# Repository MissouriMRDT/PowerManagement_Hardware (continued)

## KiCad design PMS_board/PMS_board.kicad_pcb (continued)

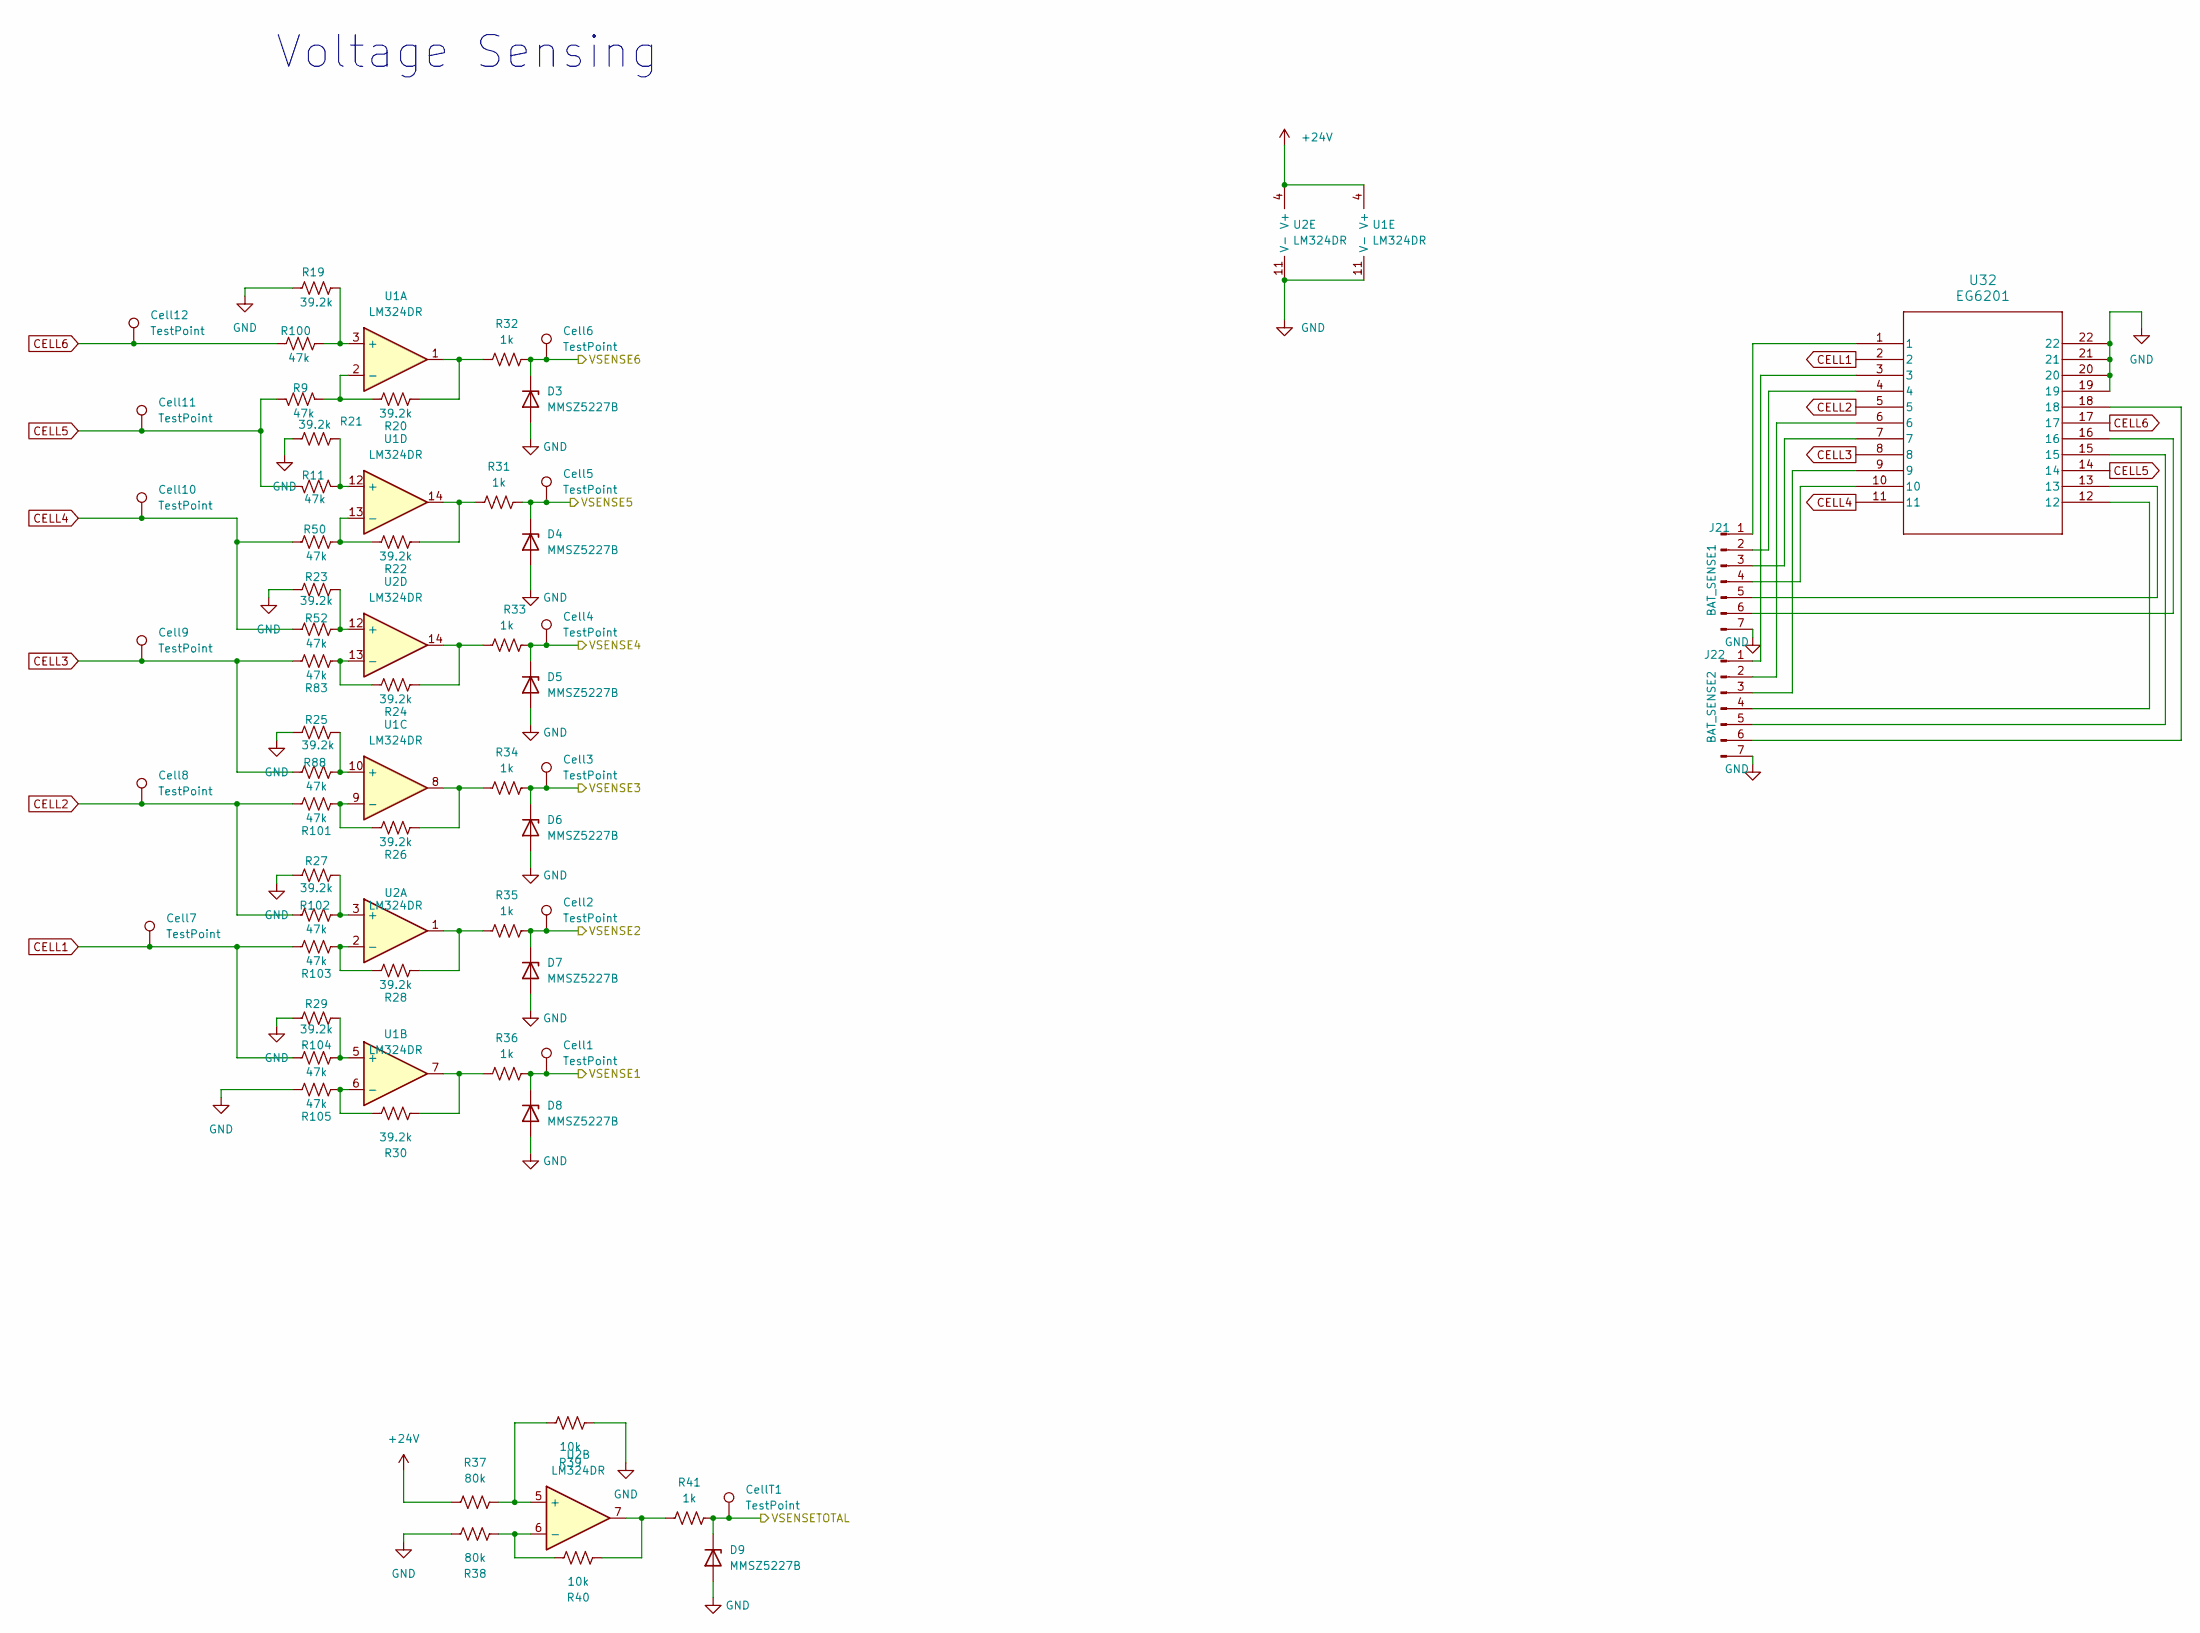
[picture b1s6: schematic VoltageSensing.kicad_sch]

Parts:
Cell1, Cell2, Cell3, Cell4, Cell5, Cell6, Cell7, Cell8, Cell9, Cell10, Cell11, Cell12: TestPoint; TestPoint_Pad_D1.0mm
CellT1: TestPoint; TestPoint_Pad_D1.0mm
D3, D4, D5, D6, D7, D8, D9: MMSZ5227B; D_SOD-123
J21: BAT_SENSE1; MOLEX_SL_07_Vertical
J22: BAT_SENSE2; MOLEX_SL_07_Vertical
R9, R11, R50, R52, R83, R88, R100, R101, R102, R103, R104, R105: 47k; R_0603_1608Metric_Pad0.98x0.95mm_HandSolder
R19, R20, R21, R22, R23, R24, R25, R26, R27, R28, R29, R30: 39.2k; R_0603_1608Metric_Pad0.98x0.95mm_HandSolder
R31, R32, R33, R34, R35, R36, R41: 1k; R_0603_1608Metric_Pad0.98x0.95mm_HandSolder
R37, R38: 80k; R_0603_1608Metric_Pad0.98x0.95mm_HandSolder
R39, R40: 10k; R_0603_1608Metric_Pad0.98x0.95mm_HandSolder
U1, U2: LM324DR; SOIC-14_3.9x8.7mm_P1.27mm
U32: EG6201; DIP_G6201_EWI

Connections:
+24V: R37.1, U1.4 (V+), U2.4 (V+); also elsewhere on the board
/Microcontroller/VSENSE1: Cell1.1 (1_1), D8.1 (K), R36.2; also elsewhere on the board
/Microcontroller/VSENSE3: Cell3.1 (1_1), D6.1 (K), R34.2; also elsewhere on the board
/Microcontroller/VSENSE4: Cell4.1 (1_1), D5.1 (K), R33.2; also elsewhere on the board
/Microcontroller/VSENSE6: Cell6.1 (1_1), D3.1 (K), R32.2; also elsewhere on the board
/Microcontroller/VSenseT: CellT1.1 (1_1), D9.1 (K), R41.2; also elsewhere on the board
CELL1: Cell7.1, R103.1, R104.1, U32.2; also elsewhere on the board
CELL3: Cell9.1, R83.1, R88.1, U32.8; also elsewhere on the board
CELL4: Cell10.1, R50.1, R52.1, U32.11; also elsewhere on the board
CELL6: Cell12.1, R100.1, U32.17; also elsewhere on the board
GND: D3.2 (A), D4.2 (A), D5.2 (A), D6.2 (A), D7.2 (A), D8.2 (A), D9.2 (A), J21.7, J22.7, R19.2, R21.2, R23.2, R25.2, R27.2, R29.2, R38.2, R39.2, R105.1, U1.11 (V-), U2.11 (V-), U32.19, U32.20, U32.21, U32.22; also elsewhere on the board
unnamed: J21.1, U32.1
unnamed: J21.2, U32.4
unnamed: J21.3, U32.7
unnamed: J21.4, U32.10
unnamed: J21.5, U32.13
unnamed: J21.6, U32.16
unnamed: J22.1, U32.3
unnamed: J22.2, U32.6
unnamed: J22.3, U32.9
unnamed: J22.4, U32.12
unnamed: J22.5, U32.15
unnamed: J22.6, U32.18
unnamed: R20.2, R32.1, U1.1
unnamed: R22.2, R31.1, U1.14
unnamed: R24.2, R33.1, U2.14
unnamed: R26.2, R34.1, U1.8
unnamed: R28.2, R35.1, U2.1
unnamed: R30.2, R36.1, U1.7
unnamed: R40.2, R41.1, U2.7
unnamed: R19.1, R100.2, U1.3 (+)
unnamed: R9.1, R20.1, U1.2 (-)
unnamed: R29.1, R104.2, U1.5 (+)
unnamed: R30.1, R105.2, U1.6 (-)
unnamed: R25.1, R88.2, U1.10 (+)
unnamed: R26.1, R101.2, U1.9 (-)
unnamed: R11.1, R21.1, U1.12 (+)
unnamed: R22.1, R50.2, U1.13 (-)
unnamed: R27.1, R102.2, U2.3 (+)
unnamed: R28.1, R103.2, U2.2 (-)
unnamed: R37.2, R39.1, U2.5 (+)
unnamed: R38.1, R40.1, U2.6 (-)
unnamed: R23.1, R52.2, U2.12 (+)
unnamed: R24.1, R83.2, U2.13 (-)

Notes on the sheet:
Voltage Sensing

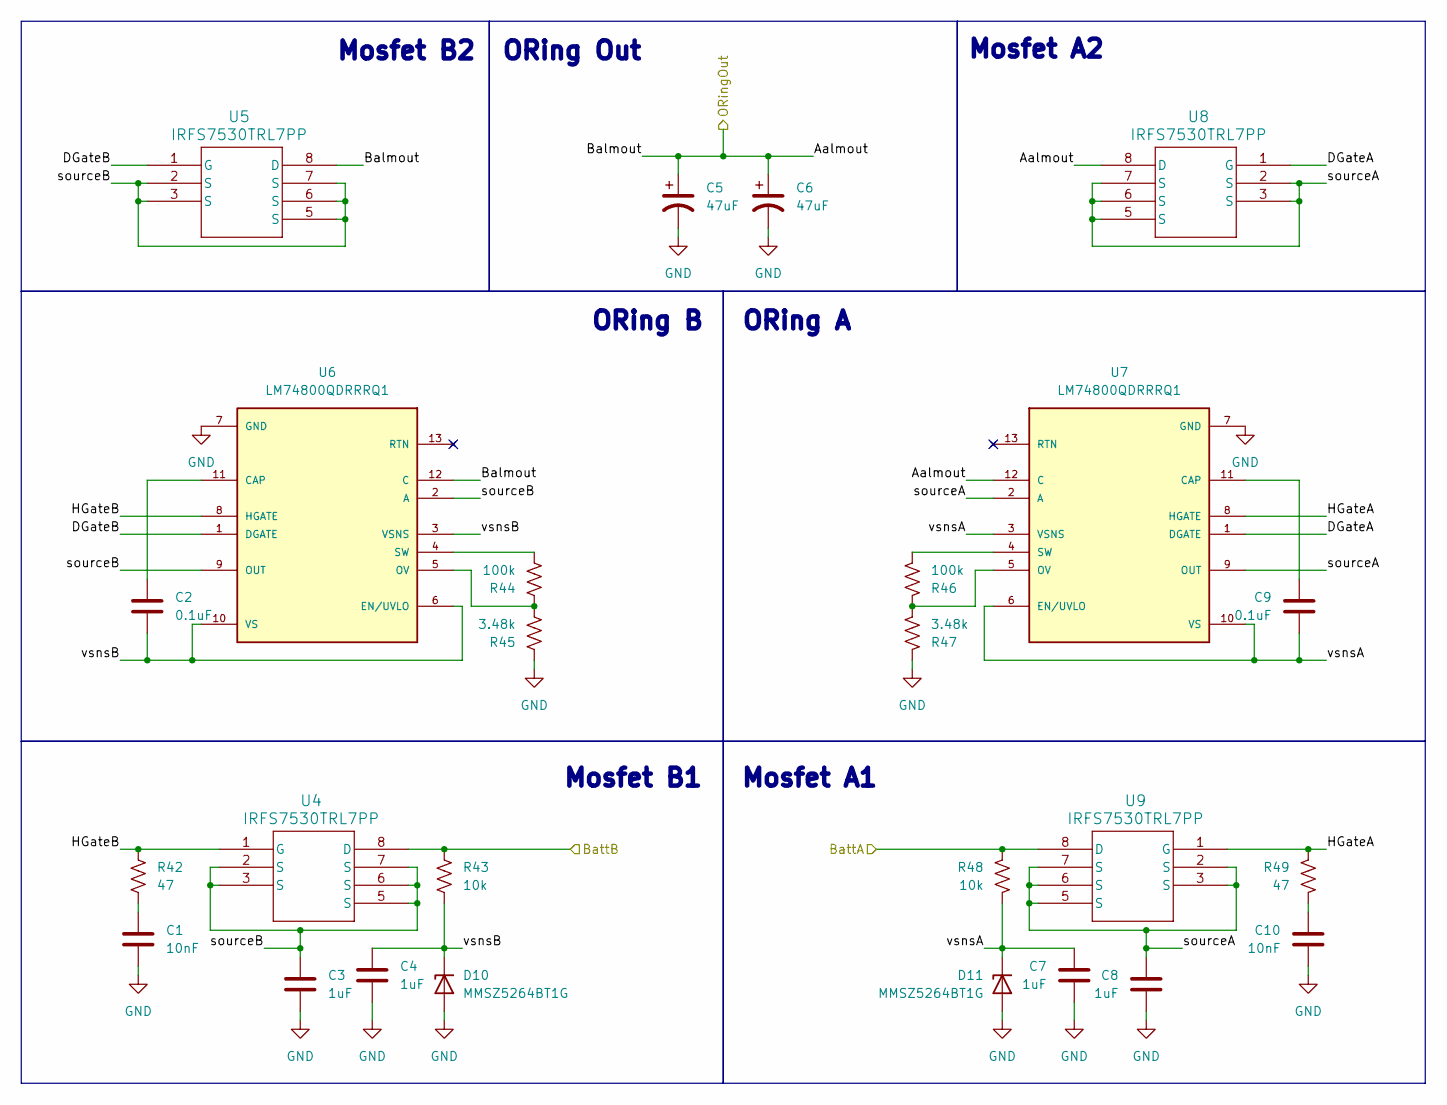
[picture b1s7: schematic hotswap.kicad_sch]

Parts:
C1, C10: 10nF; C_0603_1608Metric_Pad1.08x0.95mm_HandSolder
C2, C9: 0.1uF; C_0603_1608Metric_Pad1.08x0.95mm_HandSolder
C3, C4, C7, C8: 1uF; C_0603_1608Metric_Pad1.08x0.95mm_HandSolder
C5, C6: 47uF; C_0603_1608Metric_Pad1.08x0.95mm_HandSolder
D10, D11: MMSZ5264BT1G; D_SOD-123
R42, R49: 47; R_0603_1608Metric_Pad0.98x0.95mm_HandSolder
R43, R48: 10k; R_0603_1608Metric_Pad0.98x0.95mm_HandSolder
R44, R46: 100k; R_0603_1608Metric_Pad0.98x0.95mm_HandSolder
R45, R47: 3.48k; R_0603_1608Metric_Pad0.98x0.95mm_HandSolder
U4, U5, U8, U9: IRFS7530TRL7PP; PG-TO263-7_INF
U6, U7: LM74800QDRRRQ1; IC_LM74800QDRRRQ1; PARTREV C

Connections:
/HotSwap/Aalmout: C5.1, C6.1, U5.8 (D), U6.12 (C), U7.12 (C), U8.8 (D); also elsewhere on the board
/HotSwap/DGateA: U7.1 (DGATE), U8.1 (G)
/HotSwap/DGateB: U5.1 (G), U6.1 (DGATE)
/HotSwap/HGateA: R49.1, U7.8 (HGATE), U9.1 (G)
/HotSwap/HGateB: R42.1, U4.1 (G), U6.8 (HGATE)
/HotSwap/sourceA: C8.1, U7.2 (A), U7.9 (OUT), U8.2 (S), U8.3 (S), U8.5 (S), U8.6 (S), U8.7 (S), U9.2 (S), U9.3 (S), U9.5 (S), U9.6 (S), U9.7 (S)
/HotSwap/sourceB: C3.1, U4.2 (S), U4.3 (S), U4.5 (S), U4.6 (S), U4.7 (S), U5.2 (S), U5.3 (S), U5.5 (S), U5.6 (S), U5.7 (S), U6.2 (A), U6.9 (OUT)
/HotSwap/vsnsA: C7.1, C9.2, D11.1 (K), R48.1, U7.3 (VSNS), U7.6 (EN/UVLO), U7.10 (VS)
/HotSwap/vsnsB: C2.2, C4.1, D10.1 (K), R43.1, U6.3 (VSNS), U6.6 (EN/UVLO), U6.10 (VS)
BATTERY_IN1: R48.2, U9.8 (D); also elsewhere on the board
BATTERY_IN2: R43.2, U4.8 (D); also elsewhere on the board
GND: C1.2, C3.2, C4.2, C5.2, C6.2, C7.2, C8.2, C10.2, D10.2 (A), D11.2 (A), R45.1, R47.1, U6.7 (GND), U7.7 (GND); also elsewhere on the board
unnamed: C1.1, R42.2
unnamed: C10.1, R49.2
unnamed: C2.1, U6.11 (CAP)
unnamed: R44.1, R45.2, U6.5 (OV)
unnamed: R44.2, U6.4 (SW)
unnamed: C9.1, U7.11 (CAP)
unnamed: R46.1, R47.2, U7.5 (OV)
unnamed: R46.2, U7.4 (SW)

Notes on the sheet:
ORing B
ORing Out
Mosfet A1
Mosfet B1
ORing A
Mosfet A2
Mosfet B2

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
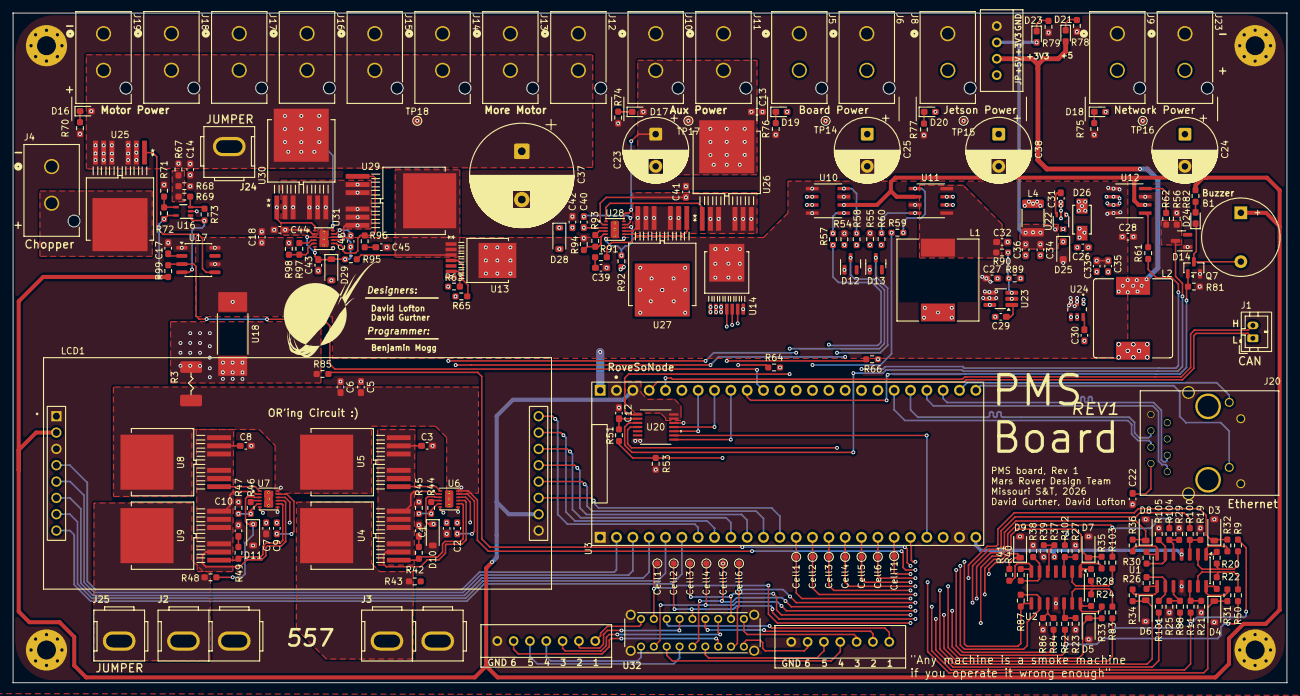
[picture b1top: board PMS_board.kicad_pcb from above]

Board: 4 copper layers, 198.1 x 104.1 mm, 235 parts (0 on the bottom side), 170 nets.

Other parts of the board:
Cell1#2, Cell2#2, Cell3#2, Cell4#2, Cell5#2, Cell6#2: TestPoint; TestPoint_Pad_D1.0mm
H1, H2, H3, H4: MountingHole_Pad; 4_40_Hole_Pad_Via
J2, J3: Conn_01x02_Pin; Square_Anderson_2_V_Side_By_Side
J25: Conn_01x01_Pin; Square_Anderson_1_V

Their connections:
BATTERY_IN1: J2.2, J25.1 (Pin_1_1); also elsewhere on the board
BATTERY_IN2: J3.2; also elsewhere on the board
CELL1: Cell1#2.1 (1_1); also elsewhere on the board
CELL3: Cell3#2.1 (1_1); also elsewhere on the board
CELL4: Cell4#2.1 (1_1); also elsewhere on the board
CELL6: Cell6#2.1 (1_1); also elsewhere on the board
GND: H1.1 (1_1), H2.1 (1_1), H3.1 (1_1), H4.1 (1_1), J2.1, J3.1; also elsewhere on the board
